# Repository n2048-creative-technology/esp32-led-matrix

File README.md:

# esp32-led-matrix

Double-sided 8x8 WS2812B LED matrix board driven by an ESP32-C6-WROOM-1,
powered over USB-C. This design merges the MCU/power subsystem from
**esp32-ce-led** with the LED-matrix/JST-PH-connector pattern from
**xiao-led-module-**, extended to a double-sided 8x8 array (128 total LEDs,
two independent 64-LED daisy chains on GPIO6/GPIO7 — one per board side).

## Board Specs

| | |
|---|---|
| MCU | ESP32-C6-WROOM-1-N8 (Wi-Fi 6 / BLE 5, RISC-V) |
| Power in | USB-C (5V), on-board AMS1117-3.3 regulator for MCU rail |
| LED driver rail | +5V direct from USB-C (WS2812B needs ~5V, not 3.3V) |
| LEDs | 128x WS2812B-2020, 8x8 grid on F.Cu + 8x8 grid on B.Cu |
| LED chains | Chain A: D10→D73 (64 LEDs, GPIO6) · Chain B: D74→D137 (64 LEDs, GPIO7) |
| USB protection | USBLC6-2SC6 ESD array on D+/D-, ESD9B3.3ST5G on VBUS |
| Status | Power LED (D1), reset button (SW1) |
| External power option | JST-PH 4-pin connector (J2) for +5V/GND injection |
| Layers | 2 (F.Cu / B.Cu), GND + 5V copper pours on both sides |
| Board size | **58.1 x 41.84mm** (compact redesign — was 46 x 91mm; see `LAYOUT_SPEC.md` §1 for the height derivation — the B.Cu component stack, not the LED grid, drives the 41.84mm figure) |
| Layout | ESP32-C6 alone on F.Cu beside LED matrix A; USB-C/JST/regulator/ESD/switch/passives on B.Cu beside LED matrix B. USB-C (J4) centered on the right edge; JST (J2) at the bottom edge. See `LAYOUT_SPEC.md` for exact coordinates. |

Component numbering is intentional: **D1** and **D4** are reused from the
MCU/power subsystem (status LED, ESD diode); **D10 through D137** are the
128 matrix LEDs. The gap (D2/D3, D5–D9) is not a bug.

## BOM

Full JLCPCB-verified BOM with LCSC part numbers: [`BOM_jlcpcb_verified.csv`](BOM_jlcpcb_verified.csv)
(also duplicated as [`production/bom.csv`](production/bom.csv) in JLCPCB
upload format: Reference/Value/Footprint/LCSC/MPN/Manufacturer).

| Ref | Part | Qty | LCSC |
|---|---|---|---|
| U1 | ESP32-C6-WROOM-1-N8 | 1 | C5366877 |
| U2 | USBLC6-2SC6-FS | 1 | C6807798 |
| U3 | AMS1117-3.3 (TO-252) | 1 | C41347676 |
| D1 | Status LED (red, 0603) | 1 | C2286 |
| D4 | ESD9B3.3ST5G | 1 | C96512 |
| D10-D137 | WS2812B-2020 (compatible) | 128 | C5349955 |
| SW1 | Tactile switch (B3U-1000P) | 1 | C231329 |
| J4 | USB-C receptacle 16-pin | 1 | C3020560 |
| J2 | JST-PH 4-pin connector | 1 | C3029442 |
| R1, R2 | 5.1K 0402 | 2 | C25905 |
| R3 | 1K 0402 | 1 | C11702 |
| R7, R8 | 10K 0402 | 2 | C25744 |
| C1, C6 | 100nF 01005 | 2 | C307376 |
| C2, C3 | 22uF 0805 | 2 | C129302 |
| C4 | 1uF 0603 | 1 | C15849 |
| C5 | 10uF 0603 | 1 | C7472959 |

Every part is Basic/Extended JLCPCB stock with a verified LCSC number; no
DNP parts in this design.

## Component Library Verification

Every symbol/footprint used is confirmed installed via KiCad's Plugin and
Content Manager on this machine (checked against the global
`sym-lib-table`/`fp-lib-table`):
- `PCM_SparkFun-LED` / `PCM_SparkFun-Connector` — SparkFun-KiCad-Libraries
  (provides the WS2812B_2020 addressable LED and JST-PH 4-pin connector)
- `PCM_Espressif` — Espressif kicad-libraries (ESP32-C6-WROOM-1 module)
- All other symbols/footprints (`Device`, `Connector`, `Power_Protection`,
  `Regulator_Linear`, `Switch`, `Capacitor_SMD`, `Resistor_SMD`, etc.) are
  built into KiCad 9 by default.

Opening this project on another machine requires installing the SparkFun and
Espressif libraries via KiCad's Plugin and Content Manager first (Tools →
Plugin and Content Manager → search "SparkFun" / "Espressif" → Install).

**JLCPCB-verified alternate library ([`lib_jlcpcb/`](lib_jlcpcb/))**: both the
LED (XL-2020RGBC-2812B, LCSC
[C5349955](https://www.lcsc.com/product-detail/C5349955.html), **128,513
units in stock**) and the JST-PH connector (WAFER-PH2.0-4PWB, LCSC
[C3029442](https://www.lcsc.com/product-detail/C3029442.html), **45,706
units in stock**) were re-verified live against the JLCPCB Open Platform API
and a complete symbol+footprint+3D-model bundle was generated directly from
LCSC's EasyEDA source data via
[`easyeda2kicad`](https://pypi.org/project/easyeda2kicad/) — each part's
`kicad_sym` carries its live datasheet URL
(`lcsc.com/datasheet/<LCSC#>.pdf`) and LCSC part number as a property, and
`jlcpcb_parts.3dshapes/` has real STEP/WRL 3D models for both parts.
  - The **LED** footprint currently in use (SparkFun's `WS2812_2020`) already
    has a complete, working datasheet link and real STEP 3D model on disk —
    it was left as-is; swapping 128 LED placements to the new footprint
    would touch copper on an already-fragile routed board for no functional
    gain (pad geometry is compatible in function but not identical in size).
  - The **JST connector** (J2) footprint (SparkFun's
    `JST_1x04_P2.0mm_Horizontal_SMD`) was missing any 3D model — this was
    fixed by attaching the new verified STEP model
    (`lib_jlcpcb/jlcpcb_parts.3dshapes/CONN-SMD_4P-P2.00_XUNPU_WAFER-PH2.0-4PWB.step`)
    directly to the existing footprint instance, a cosmetic-only change (no
    pad/copper edits — DRC results unchanged, verified before/after: 100
    violations / 61 unconnected in both cases). A full footprint swap was
    considered but rejected: the new part's pad sizes and mounting-pad
    layout differ from the current footprint, and a blind swap risked a real
    mechanical mismatch rather than just a cosmetic one.

## Manufacturing

Fabrication package in [`production/`](production/):
- [`gerbers.zip`](production/gerbers.zip) — full Gerber set + drill file (`gerbers/`)
- [`bom.csv`](production/bom.csv) — JLCPCB-format BOM
- [`positions.csv`](production/positions.csv) — CPL (component placement, both sides, mm)

Board is 2-layer, JLCPCB-standard stackup, no exotic requirements.

## DRC/ERC status

**DRC (kicad-cli pcb drc), after the compact-layout redesign (task series
1-7): board outline/LED-grid repositioning → ESP32 repositioning → B.Cu
component repositioning → stale-copper clear → Freerouting re-route +
GND/+5V zones → final cleanup:**

| Stage | Violations | Unconnected items |
|---|---|---|
| Original layout, before redesign | 100 (100 lib_footprint_mismatch only) | 61 |
| After Freerouting re-route on new 58.1x41.84mm layout (task 6) | 382 (130 shorting_items, 130 solder_mask_bridge, 100 lib_footprint_mismatch, 9 items_not_allowed, 5 silk_overlap, 4 silk_over_copper, 2 copper_edge_clearance, 1 clearance, 1 via_dangling) | 312 |
| **Final (task 7, this cleanup)** | **128** (100 lib_footprint_mismatch, 9 items_not_allowed, 5 silk_overlap, 4 silk_over_copper, 3 shorting_items, 3 solder_mask_bridge, 2 copper_edge_clearance, 1 clearance, 1 via_dangling) | **189** |

Most of the task-6 regression (382→128 violations) turned out to be a
**stale zone fill**, not real routing damage: Freerouting's SES import left
the GND/+5V copper pours unfilled, so DRC flagged hundreds of phantom
clearance/short violations against zone outlines that had no actual copper
yet. A single zone refill (`ZONE_FILLER.Fill()`) cleared the bulk of it.

The remaining 28 non-`lib_footprint_mismatch` violations are genuine and
documented, not routing bugs introduced by this redesign:
- **9 items_not_allowed + related silk_overlap/silk_over_copper (U2, U3)**:
  the regulator (U3) and USB ESD IC (U2) footprints, placed per
  `LAYOUT_SPEC.md` §10, physically overlap the ESP32's antenna-keepout zone
  on B.Cu. This is a placement conflict from an earlier task in the series,
  out of scope to fix here without moving U2/U3/re-deriving the layout spec.
- **3 shorting_items + 3 solder_mask_bridge + 1 clearance (U1 GPIO pads vs
  J4 mounting tab)**: unused ESP32 GPIO pads sit close to J4's grounded
  mechanical mounting pad (S1) on the compact board — a real minor clearance
  issue between an unused pin and a connector shield tab, not a functional
  short (the GPIO pads are unconnected in the schematic).
- **2 copper_edge_clearance (J2 NC pads)**: J2's two non-connected alignment
  pads sit 0.17mm from the board edge (0.5mm constraint) — mechanical
  alignment pads, not electrical, and the JST connector's own placement is
  otherwise correct per spec.
- **1 via_dangling**: a Freerouting-placed +5V via connected on only one
  layer, left over from the automated route.

**All 128 LED daisy-chain SIGNAL nets are fully routed** except two short
inter-LED gaps that Freerouting's SES import missed: `Net-(D79-DOUT)` was
hand-routed clean in this task (0 new violations, verified via
per-segment clearance checks before committing); `Net-(D81-DOUT)` remains
open (D81↔D82 is a long cross-board run through very dense B.Cu daisy-chain
copper — safer to hand off for a proper autorouter pass than risk another
hand-routed short in this pitch). Of the 189 unconnected items, 178 are
zone-to-zone (GND/+5V copper-pour) stitching gaps — cosmetic DRC noise from
a segmented pour, not missing electrical connections, since both zones
already blanket most of each layer. The remaining ~11 are genuine point-to-
point gaps: `Net-(D81-DOUT)` (above), USB_D+/USB_D- to U2 (blocked by the
same antenna-keepout placement conflict as above — U2's D+/D- pads sit
inside the keepout, so no track can legally terminate there without moving
U2), U3's +3V3 pin (same keepout conflict), and D1's status-LED signal
net to R3 (D1 was moved off-board during this cleanup — it had been left
at y=53mm, outside the 41.84mm board height, a leftover coordinate bug from
the original schematic; now relocated to a clear F.Cu spot at (51, 36) but
not yet routed to R3 across the dense J2/passives cluster).

**Recommended follow-up before fab**: (1) resolve the U2/U3-vs-antenna-
keepout placement conflict — either shrink/move the keepout zone per the
antenna's real RF requirements or nudge U2/U3 clear of it; (2) run one more
Freerouting pass focused on `Net-(D81-DOUT)` and the D1→R3 net; (3) hand-
place a handful more GND stitching vias at the remaining zone-pour gaps (16
were added in this task at clear board locations — spread across the
bottom margin, right edge, and mid-board — reducing the stitching-gap count
but a fully-zero unconnected count would need more targeted work than this
pass's budget allowed).

**ERC (kicad-cli sch erc): 78 violations, all benign/expected, IDENTICAL to
the pre-redesign baseline** — the schematic was never touched by this PCB
layout redesign (only footprint positions changed), so ERC output matches
byte-for-byte: unused ESP32-C6 GPIO pins (normal for an MCU breakout with
many free GPIOs), unused USB-C CC1/CC2/SBU pins (only D+/D- used), and 2
`global_label_dangling` warnings on `Net-(D73-DOUT)` / `Net-(D137-DOUT)` —
the deliberate open ends of the two LED daisy chains.

## Repo Layout

```
esp32-led-matrix.kicad_pro      KiCad project
esp32-led-matrix.kicad_sch      Schematic (MCU/power + 128x LED matrix)
esp32-led-matrix.kicad_pcb      PCB layout (compact redesign, routed via Freerouting)
LAYOUT_SPEC.md                  Exact coordinate spec for the compact-layout redesign (source of truth for component placement)
BOM_jlcpcb_verified.csv         Full BOM w/ LCSC numbers
production/                     Fab package: gerbers, drill, BOM, CPL
docs/images/                    Schematic, layout, and 3D render images
```

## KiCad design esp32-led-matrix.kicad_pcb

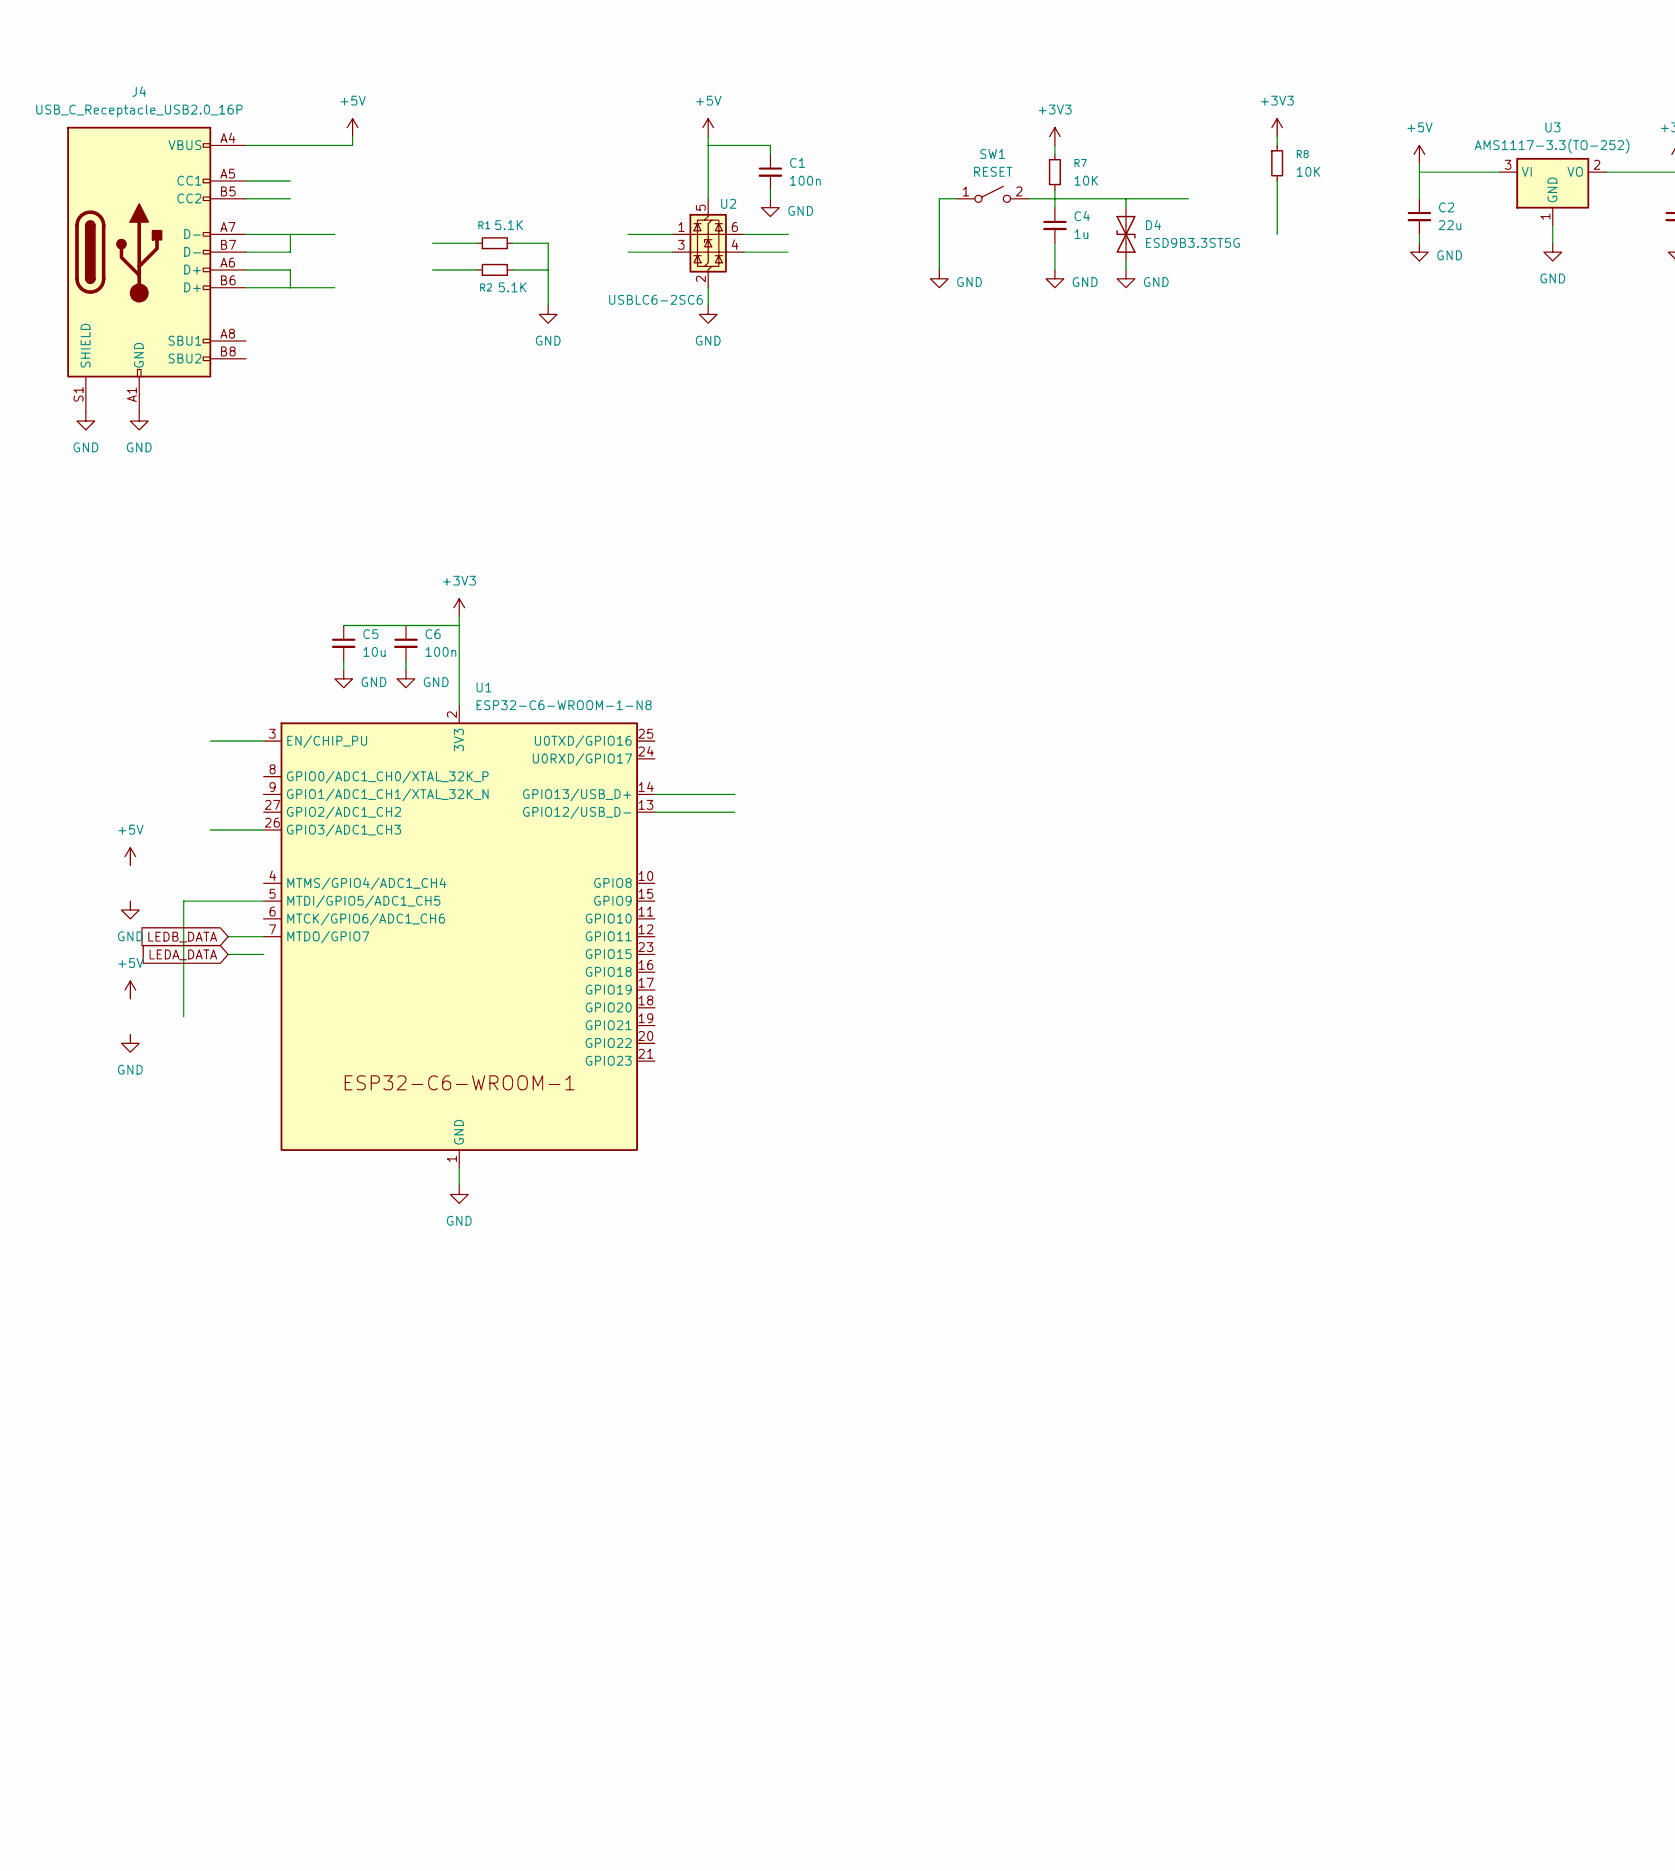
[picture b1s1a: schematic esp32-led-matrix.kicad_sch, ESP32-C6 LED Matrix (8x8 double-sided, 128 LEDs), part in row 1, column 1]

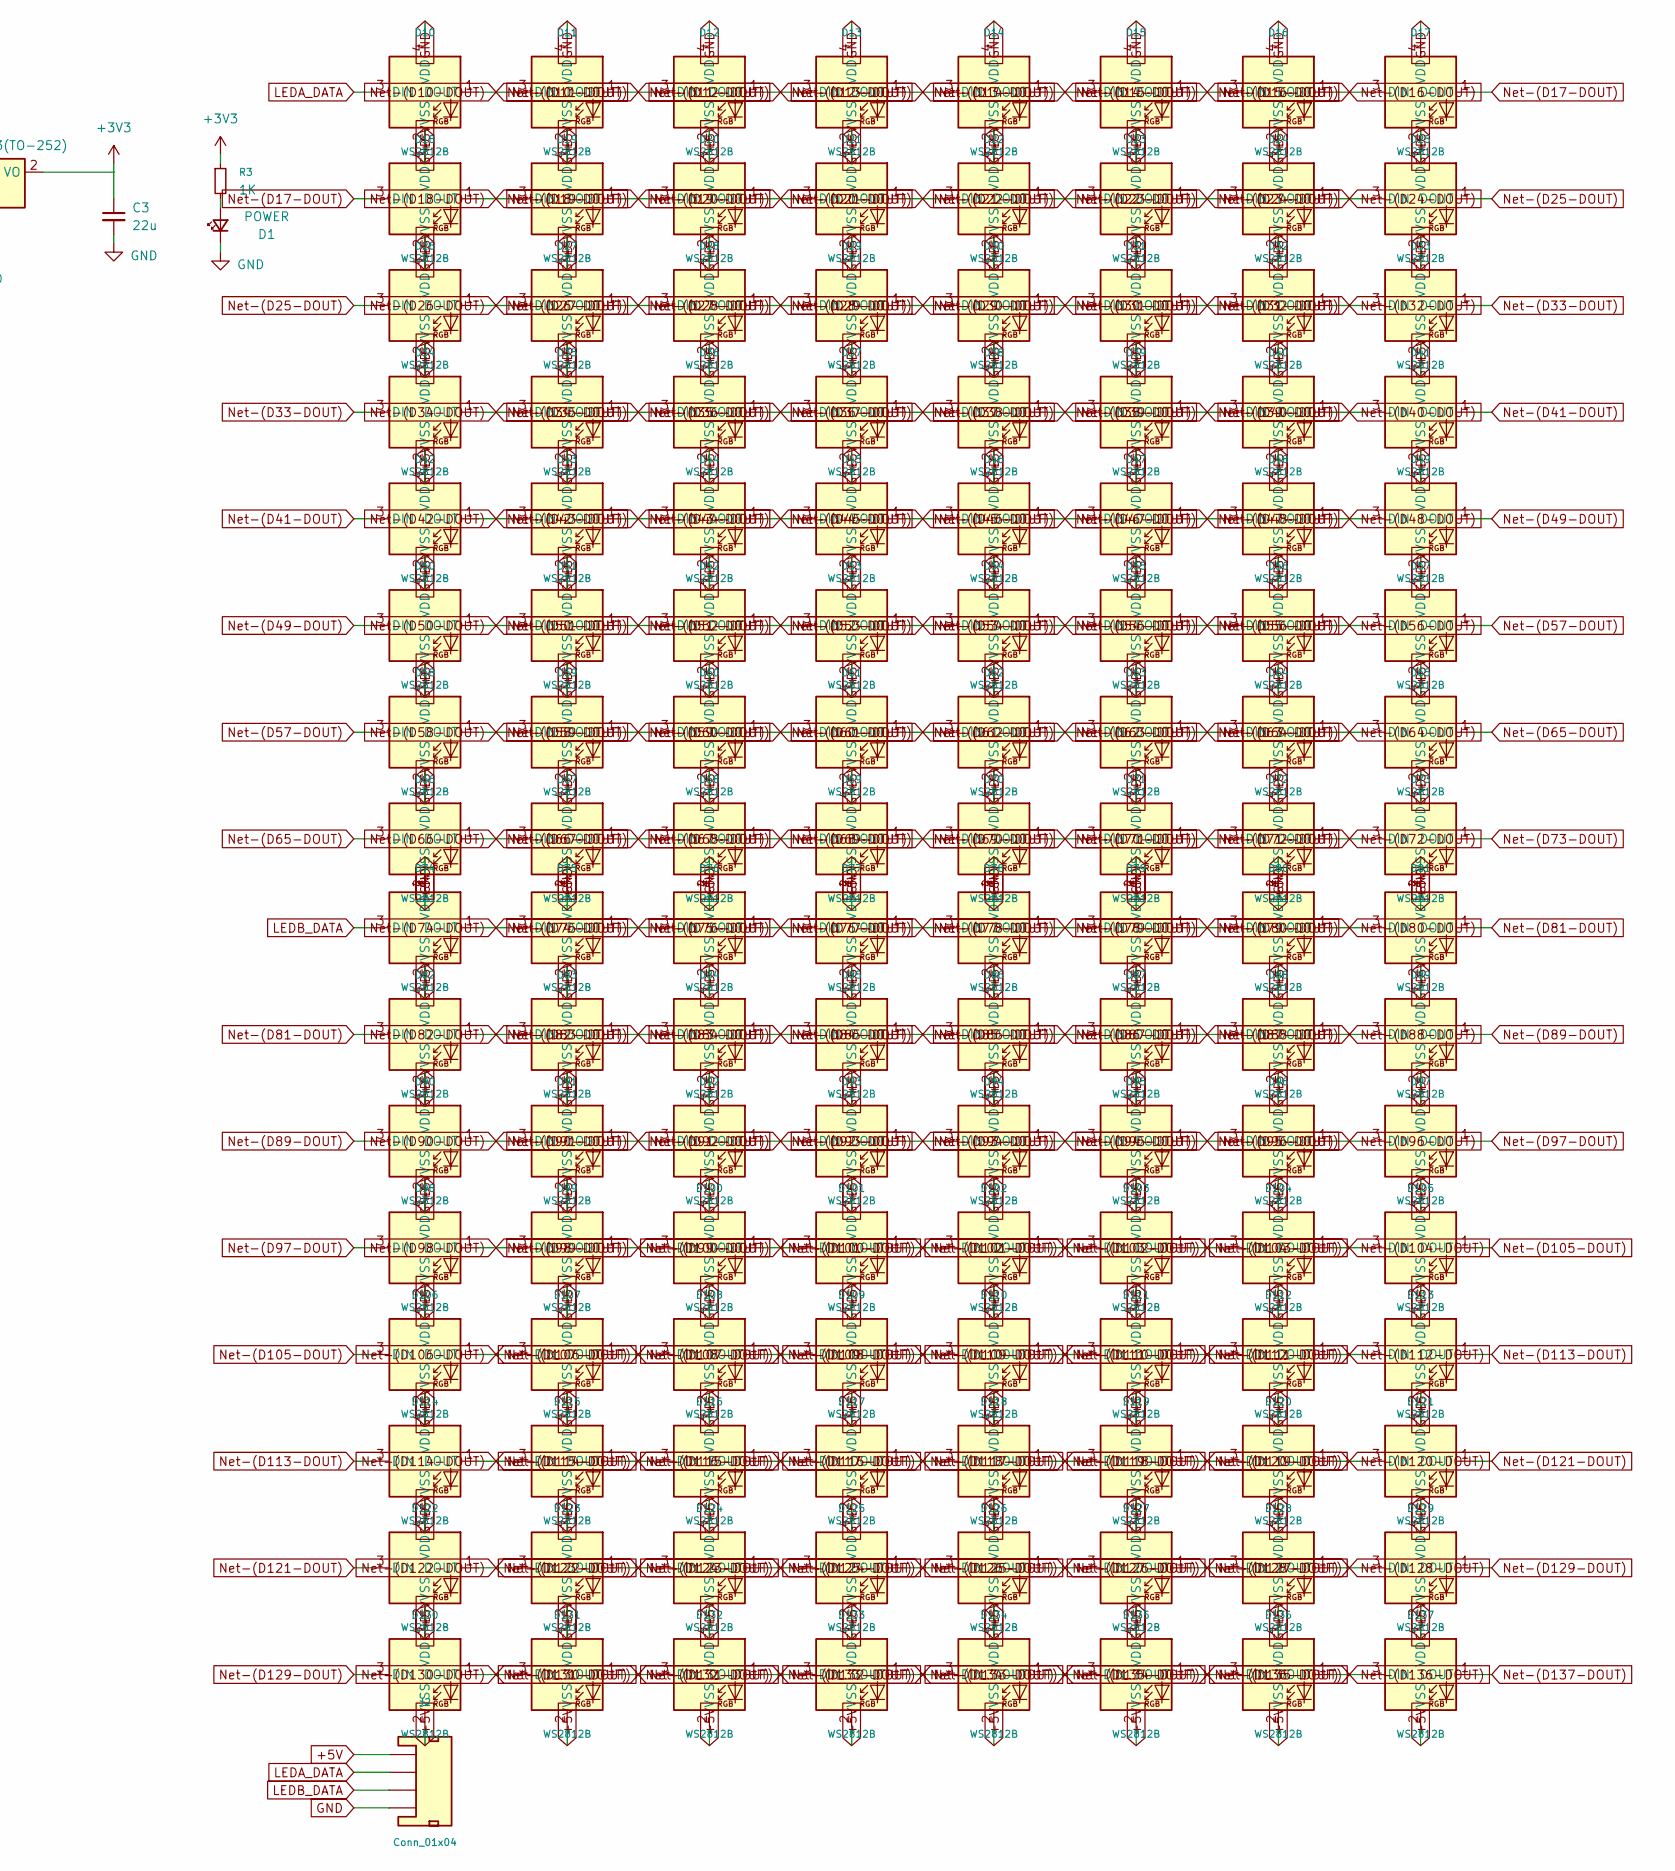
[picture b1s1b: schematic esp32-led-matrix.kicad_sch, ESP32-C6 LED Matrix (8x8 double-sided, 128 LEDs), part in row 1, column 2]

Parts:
C1, C6: 100n; C_01005_0402Metric; MPN CL02A104MQ2NNNC; LCSC C307376
C2, C3: 22u; C_0805_2012Metric; MPN 0805X226M160NT; LCSC C129302
C4: 1u; C_0603_1608Metric; MPN CL10A105KB8NNNC; LCSC C15849
C5: 10u; C_0603_1608Metric; MPN HGC0603R5106M160NTHJ; LCSC C7472959
D1: POWER; LED_0603_1608Metric; MPN KT-0603R; LCSC C2286
D4: ESD9B3.3ST5G; D_SOD-923; MPN ESD9B3.3ST5G; LCSC C96512
D10, D11, D12, D13, D14, D15, D16, D17, D18, D19, D20, D21, D22, D23, D24, D25, D26, D27, D28, D29, D30, D31, D32, D33, D34, D35, D36, D37, D38, D39, D40, D41, D42, D43, D44, D45, D46, D47, D48, D49, D50, D51, D52, D53, D54, D55, D56, D57, D58, D59, D60, D61, D62, D63, D64, D65, D66, D67, D68, D69, D70, D71, D72, D73, D74, D75, D76, D77, D78, D79, D80, D81, D82, D83, D84, D85, D86, D87, D88, D89, D90, D91, D92, D93, D94, D95, D96, D97, D98, D99, D100, D101, D102, D103, D104, D105, D106, D107, D108, D109, D110, D111, D112, D113, D114, D115, D116, D117, D118, D119, D120, D121, D122, D123, D124, D125, D126, D127, D128, D129, D130, D131, D132, D133, D134, D135, D136, D137: WS2812B; WS2812_2020; MPN XL-2020RGBC-2812B; LCSC C5349955
J2: Conn_01x04; JST_1x04_P2.0mm_Horizontal_SMD; MPN WAFER-PH2.0-4PWB; LCSC C3029442
J4: USB_C_Receptacle_USB2.0_16P; USB_C_Receptacle_GCT_USB4105-xx-A_16P_TopMnt_Horizontal; MPN USB4105-GF-A; LCSC C3020560
R1, R2: 5.1K; R_0402_1005Metric_Pad0.72x0.64mm_HandSolder; MPN 0402WGF5101TCE; LCSC C25905
R3: 1K; R_0402_1005Metric_Pad0.72x0.64mm_HandSolder; MPN 0402WGF1001TCE; LCSC C11702
R7, R8: 10K; R_0402_1005Metric_Pad0.72x0.64mm_HandSolder; MPN 0402WGF1002TCE; LCSC C25744
SW1: RESET; SW_SPST_B3U-1000P; MPN B3U-1000P; LCSC C231329
U1: ESP32-C6-WROOM-1-N8; ESP32-C6-WROOM-1; MPN ESP32-C6-WROOM-1-N8; LCSC C5366877
U2: USBLC6-2SC6; SOT-23-6; MPN USBLC6-2SC6-FS; LCSC C6807798
U3: AMS1117-3.3(TO-252); TO-252-3_TabPin2; MPN AMS1117-3.3(TO-252); LCSC C41347676

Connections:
+3V3: C3.1, C5.1, C6.1, R3.1, R7.1, R8.1, U1.2 (3V3), U3.2 (VO)
CC1: J4.A5 (CC1), R1.1
CC2: J4.B5 (CC2), R2.1
GPIO3: R8.2, U1.26 (GPIO3/ADC1_CH3)
LEDA_DATA: D10.3 (DIN), J2.2, U1.6 (MTCK/GPIO6/ADC1_CH6)
LEDB_DATA: D74.3 (DIN), J2.3, U1.7 (MTDO/GPIO7)
unnamed: D1.2 (A), R3.2
unnamed: D10.1 (DOUT), D11.3 (DIN)
unnamed: D11.1 (DOUT), D12.3 (DIN)
unnamed: D12.1 (DOUT), D13.3 (DIN)
unnamed: D13.1 (DOUT), D14.3 (DIN)
unnamed: D14.1 (DOUT), D15.3 (DIN)
unnamed: D15.1 (DOUT), D16.3 (DIN)
unnamed: D16.1 (DOUT), D17.3 (DIN)
unnamed: D17.1 (DOUT), D18.3 (DIN)
unnamed: D18.1 (DOUT), D19.3 (DIN)
unnamed: D19.1 (DOUT), D20.3 (DIN)
unnamed: D20.1 (DOUT), D21.3 (DIN)
unnamed: D21.1 (DOUT), D22.3 (DIN)
unnamed: D22.1 (DOUT), D23.3 (DIN)
unnamed: D23.1 (DOUT), D24.3 (DIN)
unnamed: D24.1 (DOUT), D25.3 (DIN)
unnamed: D25.1 (DOUT), D26.3 (DIN)
unnamed: D26.1 (DOUT), D27.3 (DIN)
unnamed: D27.1 (DOUT), D28.3 (DIN)
unnamed: D28.1 (DOUT), D29.3 (DIN)
unnamed: D29.1 (DOUT), D30.3 (DIN)
unnamed: D30.1 (DOUT), D31.3 (DIN)
unnamed: D31.1 (DOUT), D32.3 (DIN)
unnamed: D32.1 (DOUT), D33.3 (DIN)
unnamed: D33.1 (DOUT), D34.3 (DIN)
unnamed: D34.1 (DOUT), D35.3 (DIN)
unnamed: D35.1 (DOUT), D36.3 (DIN)
unnamed: D36.1 (DOUT), D37.3 (DIN)
unnamed: D37.1 (DOUT), D38.3 (DIN)
unnamed: D38.1 (DOUT), D39.3 (DIN)
unnamed: D39.1 (DOUT), D40.3 (DIN)
unnamed: D40.1 (DOUT), D41.3 (DIN)
unnamed: D41.1 (DOUT), D42.3 (DIN)
unnamed: D42.1 (DOUT), D43.3 (DIN)
unnamed: D43.1 (DOUT), D44.3 (DIN)
unnamed: D44.1 (DOUT), D45.3 (DIN)
unnamed: D45.1 (DOUT), D46.3 (DIN)
unnamed: D46.1 (DOUT), D47.3 (DIN)
unnamed: D47.1 (DOUT), D48.3 (DIN)
unnamed: D48.1 (DOUT), D49.3 (DIN)
unnamed: D49.1 (DOUT), D50.3 (DIN)
unnamed: D50.1 (DOUT), D51.3 (DIN)
unnamed: D51.1 (DOUT), D52.3 (DIN)
unnamed: D52.1 (DOUT), D53.3 (DIN)
unnamed: D53.1 (DOUT), D54.3 (DIN)
unnamed: D54.1 (DOUT), D55.3 (DIN)
unnamed: D55.1 (DOUT), D56.3 (DIN)
unnamed: D56.1 (DOUT), D57.3 (DIN)
unnamed: D57.1 (DOUT), D58.3 (DIN)
unnamed: D58.1 (DOUT), D59.3 (DIN)
unnamed: D59.1 (DOUT), D60.3 (DIN)
unnamed: D60.1 (DOUT), D61.3 (DIN)
unnamed: D61.1 (DOUT), D62.3 (DIN)
unnamed: D62.1 (DOUT), D63.3 (DIN)
unnamed: D63.1 (DOUT), D64.3 (DIN)
unnamed: D64.1 (DOUT), D65.3 (DIN)
unnamed: D65.1 (DOUT), D66.3 (DIN)
unnamed: D66.1 (DOUT), D67.3 (DIN)
unnamed: D67.1 (DOUT), D68.3 (DIN)
unnamed: D68.1 (DOUT), D69.3 (DIN)
unnamed: D69.1 (DOUT), D70.3 (DIN)
unnamed: D70.1 (DOUT), D71.3 (DIN)
unnamed: D71.1 (DOUT), D72.3 (DIN)
unnamed: D72.1 (DOUT), D73.3 (DIN)
unnamed: D74.1 (DOUT), D75.3 (DIN)
unnamed: D75.1 (DOUT), D76.3 (DIN)
unnamed: D76.1 (DOUT), D77.3 (DIN)
unnamed: D77.1 (DOUT), D78.3 (DIN)
unnamed: D78.1 (DOUT), D79.3 (DIN)
unnamed: D79.1 (DOUT), D80.3 (DIN)
unnamed: D80.1 (DOUT), D81.3 (DIN)
unnamed: D81.1 (DOUT), D82.3 (DIN)
unnamed: D82.1 (DOUT), D83.3 (DIN)
unnamed: D83.1 (DOUT), D84.3 (DIN)
unnamed: D84.1 (DOUT), D85.3 (DIN)
unnamed: D85.1 (DOUT), D86.3 (DIN)
unnamed: D86.1 (DOUT), D87.3 (DIN)
unnamed: D87.1 (DOUT), D88.3 (DIN)
unnamed: D88.1 (DOUT), D89.3 (DIN)
unnamed: D89.1 (DOUT), D90.3 (DIN)
unnamed: D90.1 (DOUT), D91.3 (DIN)
unnamed: D91.1 (DOUT), D92.3 (DIN)
unnamed: D92.1 (DOUT), D93.3 (DIN)
unnamed: D93.1 (DOUT), D94.3 (DIN)
unnamed: D94.1 (DOUT), D95.3 (DIN)
unnamed: D95.1 (DOUT), D96.3 (DIN)
unnamed: D96.1 (DOUT), D97.3 (DIN)
unnamed: D97.1 (DOUT), D98.3 (DIN)
unnamed: D98.1 (DOUT), D99.3 (DIN)
unnamed: D99.1 (DOUT), D100.3 (DIN)
unnamed: D100.1 (DOUT), D101.3 (DIN)
unnamed: D101.1 (DOUT), D102.3 (DIN)
unnamed: D102.1 (DOUT), D103.3 (DIN)
unnamed: D103.1 (DOUT), D104.3 (DIN)
unnamed: D104.1 (DOUT), D105.3 (DIN)
unnamed: D105.1 (DOUT), D106.3 (DIN)
unnamed: D106.1 (DOUT), D107.3 (DIN)
unnamed: D107.1 (DOUT), D108.3 (DIN)
unnamed: D108.1 (DOUT), D109.3 (DIN)
unnamed: D109.1 (DOUT), D110.3 (DIN)
unnamed: D110.1 (DOUT), D111.3 (DIN)
unnamed: D111.1 (DOUT), D112.3 (DIN)
unnamed: D112.1 (DOUT), D113.3 (DIN)
unnamed: D113.1 (DOUT), D114.3 (DIN)
unnamed: D114.1 (DOUT), D115.3 (DIN)
unnamed: D115.1 (DOUT), D116.3 (DIN)
unnamed: D116.1 (DOUT), D117.3 (DIN)
unnamed: D117.1 (DOUT), D118.3 (DIN)
unnamed: D118.1 (DOUT), D119.3 (DIN)
unnamed: D119.1 (DOUT), D120.3 (DIN)
unnamed: D120.1 (DOUT), D121.3 (DIN)
unnamed: D121.1 (DOUT), D122.3 (DIN)
unnamed: D122.1 (DOUT), D123.3 (DIN)
unnamed: D123.1 (DOUT), D124.3 (DIN)
unnamed: D124.1 (DOUT), D125.3 (DIN)
unnamed: D125.1 (DOUT), D126.3 (DIN)
unnamed: D126.1 (DOUT), D127.3 (DIN)
unnamed: D127.1 (DOUT), D128.3 (DIN)
unnamed: D128.1 (DOUT), D129.3 (DIN)
unnamed: D129.1 (DOUT), D130.3 (DIN)
unnamed: D130.1 (DOUT), D131.3 (DIN)
unnamed: D131.1 (DOUT), D132.3 (DIN)
unnamed: D132.1 (DOUT), D133.3 (DIN)
unnamed: D133.1 (DOUT), D134.3 (DIN)
unnamed: D134.1 (DOUT), D135.3 (DIN)
unnamed: D135.1 (DOUT), D136.3 (DIN)
unnamed: D136.1 (DOUT), D137.3 (DIN)
USB_D+: U1.14 (GPIO13/USB_D+), U2.6 (I/O1)
USB_D-: U1.13 (GPIO12/USB_D-), U2.4 (I/O2)

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
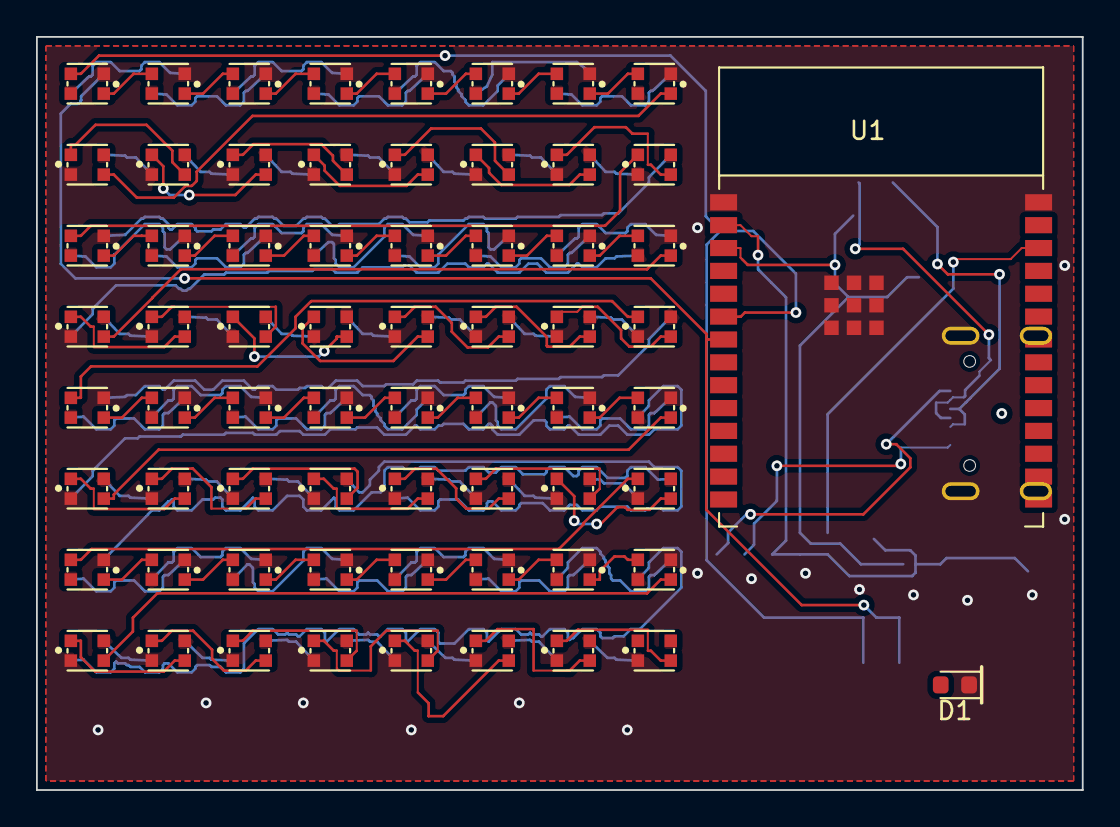
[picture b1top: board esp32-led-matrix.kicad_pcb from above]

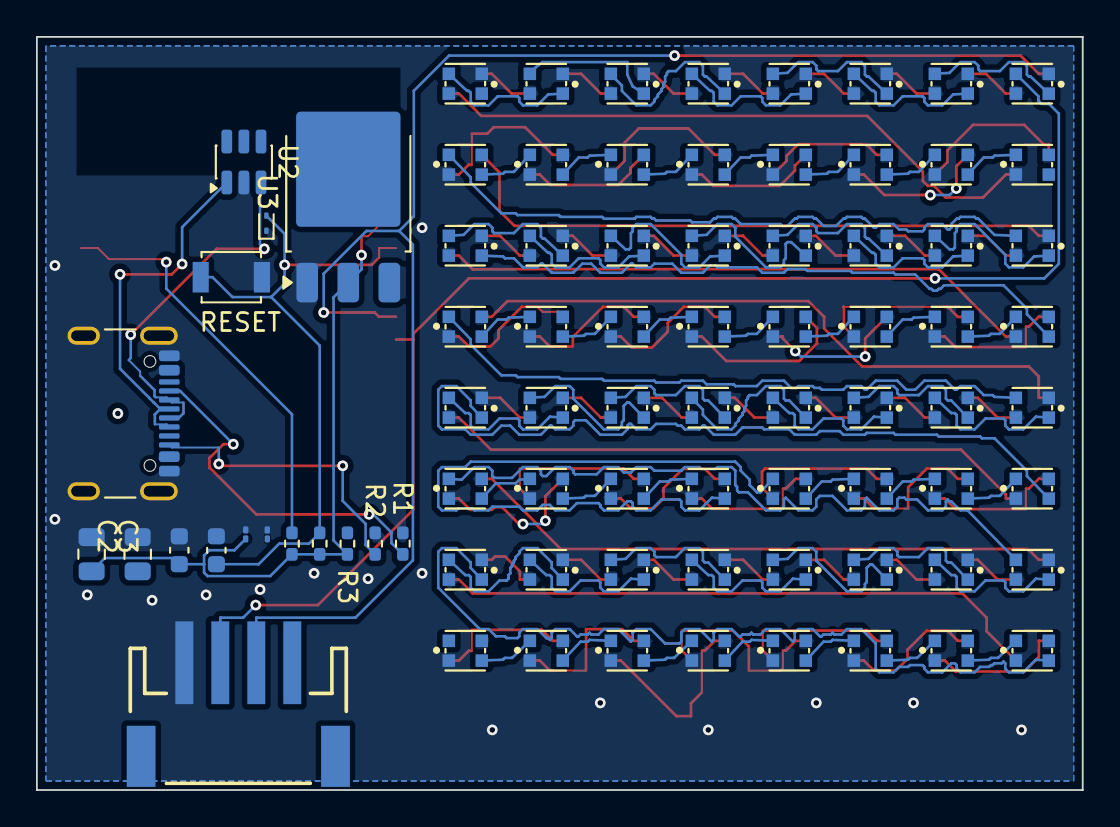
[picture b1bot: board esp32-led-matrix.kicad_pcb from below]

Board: 2 copper layers, 58.1 x 41.8 mm, 147 parts (81 on the bottom side), 140 nets.

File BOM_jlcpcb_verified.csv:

"Reference","Value","Footprint","LCSC","MPN","Manufacturer"
"C1,C6","100n","Capacitor_SMD:C_01005_0402Metric","C307376","CL02A104MQ2NNNC",""
"C2,C3","22u","Capacitor_SMD:C_0805_2012Metric","C129302","0805X226M160NT",""
"C4","1u","Capacitor_SMD:C_0603_1608Metric","C15849","CL10A105KB8NNNC",""
"C5","10u","Capacitor_SMD:C_0603_1608Metric","C7472959","HGC0603R5106M160NTHJ",""
"D1","POWER","LED_SMD:LED_0603_1608Metric","C2286","KT-0603R",""
"D4","ESD9B3.3ST5G","Diode_SMD:D_SOD-923","C96512","ESD9B3.3ST5G",""
"D10-D137","WS2812B","PCM_SparkFun-LED:WS2812_2020","C5349955","XL-2020RGBC-2812B",""
"J2","Conn_01x04","PCM_SparkFun-Connector:JST_1x04_P2.0mm_Horizontal_SMD","C3029442","WAFER-PH2.0-4PWB",""
"J4","USB_C_Receptacle_USB2.0_16P","Connector_USB:USB_C_Receptacle_GCT_USB4105-xx-A_16P_TopMnt_Horizontal","C3020560","USB4105-GF-A",""
"R1,R2","5.1K","Resistor_SMD:R_0402_1005Metric_Pad0.72x0.64mm_HandSolder","C25905","0402WGF5101TCE",""
"R3","1K","Resistor_SMD:R_0402_1005Metric_Pad0.72x0.64mm_HandSolder","C11702","0402WGF1001TCE",""
"R7,R8","10K","Resistor_SMD:R_0402_1005Metric_Pad0.72x0.64mm_HandSolder","C25744","0402WGF1002TCE",""
"SW1","RESET","Button_Switch_SMD:SW_SPST_B3U-1000P","C231329","B3U-1000P",""
"U1","ESP32-C6-WROOM-1-N8","PCM_Espressif:ESP32-C6-WROOM-1","C5366877","ESP32-C6-WROOM-1-N8","Espressif Systems"
"U2","USBLC6-2SC6","Package_TO_SOT_SMD:SOT-23-6","C6807798","USBLC6-2SC6-FS",""
"U3","AMS1117-3.3(TO-252)","Package_TO_SOT_SMD:TO-252-3_TabPin2","C41347676","AMS1117-3.3(TO-252)",""
